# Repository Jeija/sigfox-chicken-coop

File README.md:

# Sigfox-Enabled Chicken Coop Controller

This repository contains hardware design files as well as firmware source code for a chicken coop controller board. The tiny controller (approx. 50x50mm) automatically opens and closes the chicken coop's door at scheduled times of day. It also transmits environmental data (e.g. temperature, humidity) via the Sigfox network and uses a solar chell to recharge a connected lead-acid battery.

The device operates in conjunction with a web service that uses the Sigfox API to retrieve the latest messages and that provides the current configuration and time of day to the controller. The web service has an end user-facing frontend that displays environmental data, device status information and lets the user configure door opening / closing times.

As a whole, this project probably isn't particularly useful for you since it represents a rather customized solution. Parts of it though may be of interest, e.g. the S2-LP transmitter design, the solar charger design or the firmware, which can be used as reference for how to integrate [renard-phy-s2lp](https://github.com/jeija/renard-phy-s2lp), an open source Sigfox PHY based on the open-source Sigfox stack [librenard](https://github.com/jeija/librenard) into an ESP32 project.

## Hardware Design
The controller mainly consists of the following components:

* An ESP32 microcontroller with integrated WiFi. WiFi functionality is only used for Over-the-Air (OTA) updating
* An S2-LP transceiver for Sigfox uplink and downlink, the RX balun / impedance matching is implemented with discrete components
* A LT3652 solar charging controller for lead-acid battery charging
* A RV-3029-C2 Real Time Clock (RTC)
* A BME280 environmental sensor for measuring temperature, pressure and humidity
* A DRV8872 as DC motor driver with an INA219 for motor current measurement (stall detection) for the door, as well as an input for a reed contact

Everything is mounted on a tiny 50x50mm PCB which fits nicely into an off-the-shelf plastic case (Strapubox A515).

The system is is powered by a 12V/7.2Ah lead-acid battery, which is recharged by the solar panel on top of the chicken coop. The Sigfox antenna is also mounted outside for an increased link budget.

* [**Download PDF Schematic**](hardware_pdf/schematic.pdf)
* [**Download PDF PCB Layout**](hardware_pdf/pcb.pdf)
* [**KiCad Sources**](hardware)

## Firmware
The controller firmware is based on [esp-idf](https://github.com/espressif/esp-idf).
Sigfox functionality is based on [renard-phy-s2lp](https://github.com/jeija/renard-phy-s2lp) and [renard-phy-s2lp-hal-esp32](https://github.com/jeija/renard-phy-s2lp-hal-esp32), which are included as git subprojects. This means that you need to make sure to clone this repository with the `--recursive` flag.

The firmware supports Over-the-Air (OTA) updates via WiFi. This functionality is based on [esp32-softap-ota](https://github.com/Jeija/esp32-softap-ota).

### Configuration
For now, Sigfox device ID and secret key are configured directly in `firmware/main/src/sigfox.c`, see variables `sigfox_key` and `sigfox_devid`. The provided default values are those that I published during [my Sigfox reverse engineering presentation](https://jeija.net/sigfox/), so they are known to be compromised!

Watch that presentation to learn more about device ID and secret key (=NAK) and where to obtain yours.

### Initial Build and Flash
Make sure you have a recent [esp-idf](https://github.com/espressif/esp-idf) version with support for cmake-based projects installed and configured properly. Then compile and flash this project as usual using the following steps:

* `idf.py all` to compile everything
* `idf.py -p /dev/ttyUSBX flash` to flash everything

### Over-the-Air Firmware Update
Compile the firmware as described previously and obtain the firmware binary at `firmware/build/sigfox-chicken-door.bin`.

Press both buttons of the chicken coop (up and down) simultaneously until the controller starts beeping regularly. This indicates that it is ready to receive updates.

The controller broadcasts a WiFi network with SSID `ESP32 OTA Update` and acts as an HTTP server. Connect to it, open the webpage at [192.168.4.1](http://192.168.4.1) and use the form to upload the binary. The webpage will display the update progress.

You can also use the `compile_and_post.sh` script to automatically perform the OTA firmware update, which might be useful during development.

## Web Component
The web component is a node.js application that runs on any web server that connects to the Sigfox API to provide downlinks (e.g. open / close time configuration) to the controller, analyze uplinks and visualize information.

This component is currently not public, but feel free to contact me if you have any questions regarding it.

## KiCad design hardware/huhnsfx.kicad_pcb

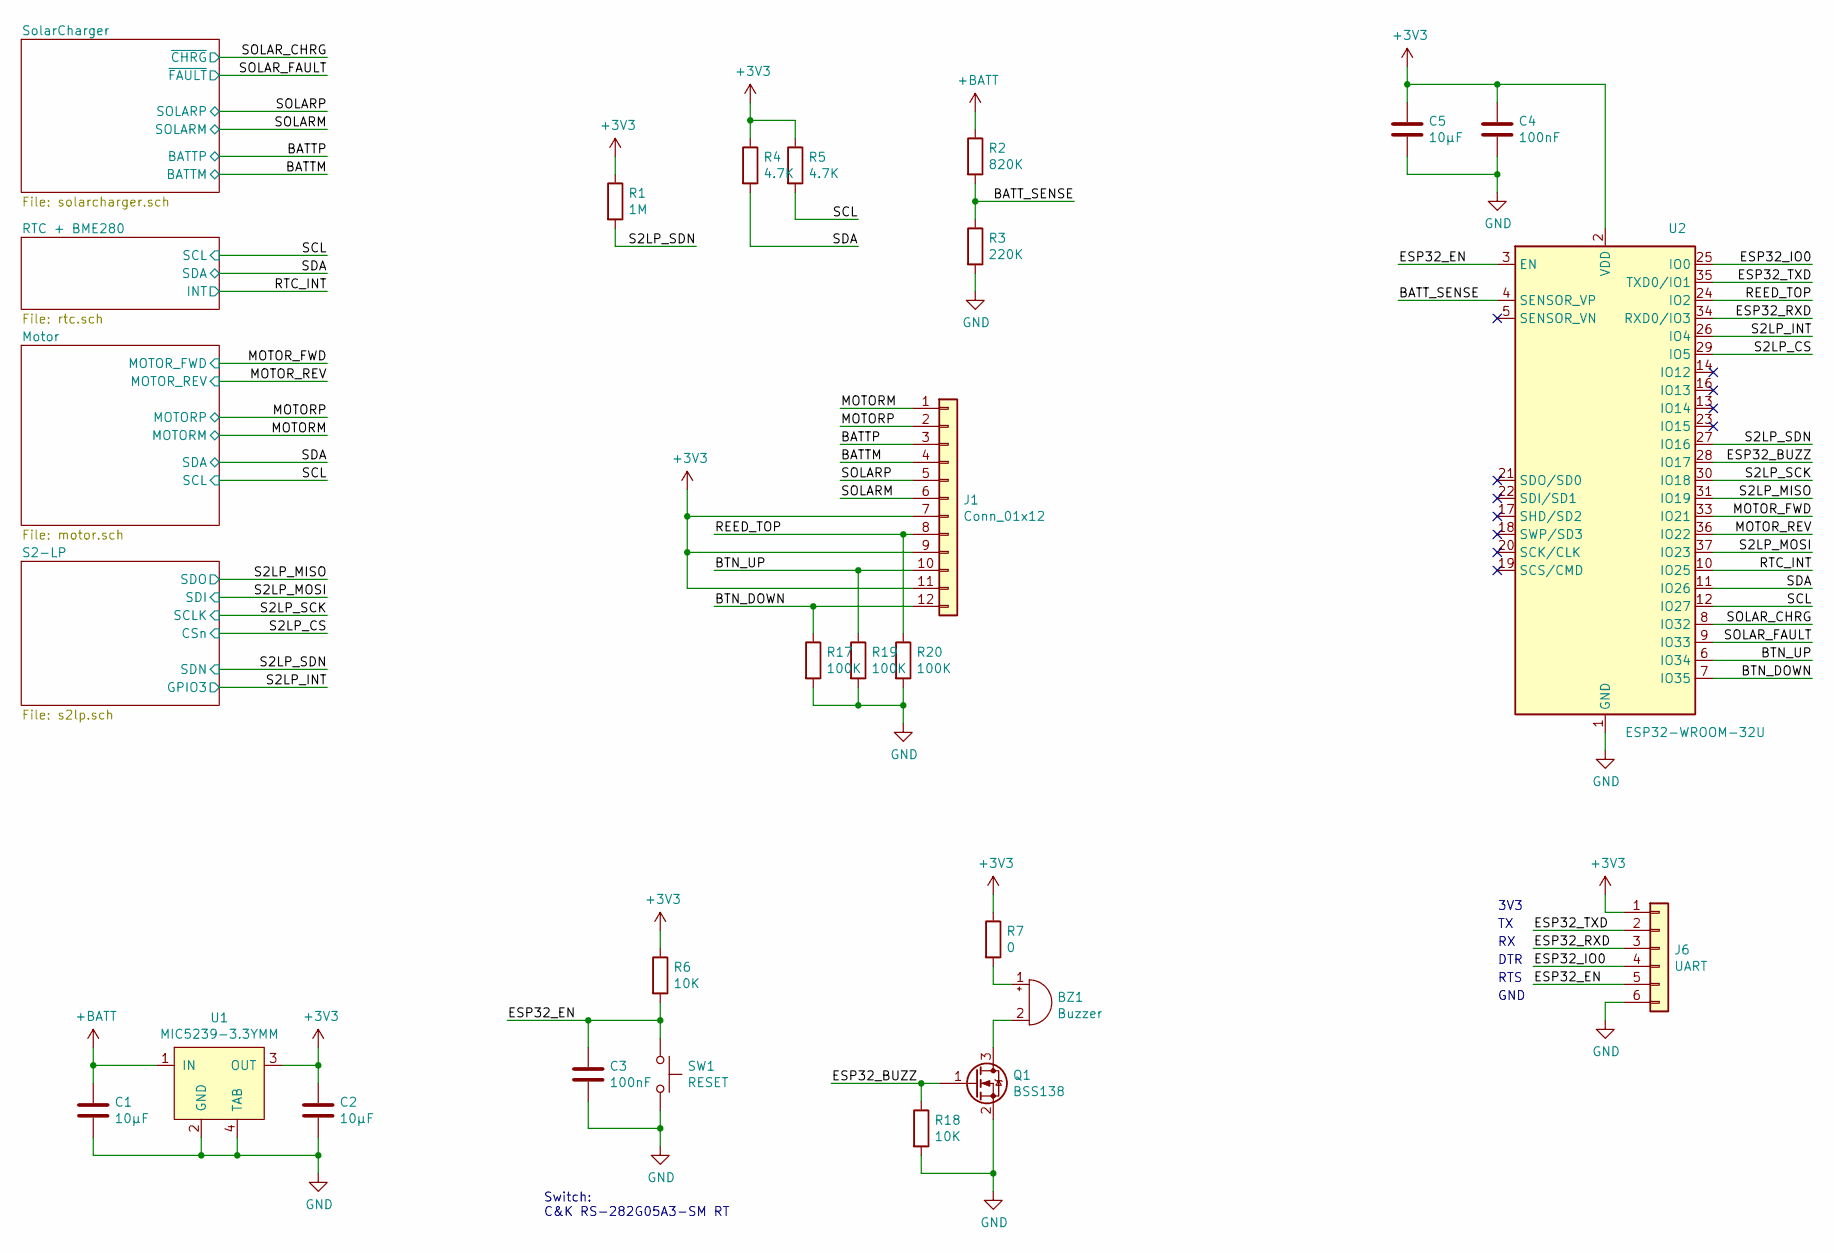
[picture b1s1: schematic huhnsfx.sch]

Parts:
BZ1: Buzzer; CMT-4023S
C1, C2, C5: 10µF; C_0603_1608Metric
C3, C4: 100nF; C_0603_1608Metric
J1: Conn_01x12; WAGO-233-512
J6: UART; PinHeader_2x03_P1.27mm_Vertical
Q1: BSS138; SOT-23
R1: 1M; R_0603_1608Metric
R2: 820K; R_0603_1608Metric
R3: 220K; R_0603_1608Metric
R4, R5: 4.7K; R_0603_1608Metric
R6, R18: 10K; R_0603_1608Metric
R7: 0; R_0603_1608Metric
R17, R19, R20: 100K; R_0603_1608Metric
SW1: RESET; SW_SPST_CK_RS282G05A3
U1: MIC5239-3.3YMM; SOT-223
U2: ESP32-WROOM-32U

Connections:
+3V3: C2.1, C4.1, C5.1, J1.7, J1.9, J1.11, J6.1, R1.1, R4.1, R5.1, R6.1, R7.1, U1.3 (OUT), U2.2 (VDD); also elsewhere on the board
+BATT: C1.1, J1.3, R2.1, U1.1 (IN); also elsewhere on the board
/BATT_SENSE: R2.2, R3.1, U2.4 (SENSOR_VP)
/BTN_DOWN: J1.12, R17.1, U2.7 (IO35)
/BTN_UP: J1.10, R19.1, U2.6 (IO34)
/ESP32_BUZZ: Q1.1 (G), R18.1, U2.28 (IO17)
/ESP32_EN: C3.1, J6.5, R6.2, SW1.1, U2.3 (EN)
/ESP32_IO0: J6.4, U2.25 (IO0)
/ESP32_RXD: J6.3, U2.34 (RXD0/IO3)
/ESP32_TXD: J6.2, U2.35 (TXD0/IO1)
/MOTORM: J1.1; also elsewhere on the board
/MOTORP: J1.2; also elsewhere on the board
/MOTOR_FWD: U2.33 (IO21); also elsewhere on the board
/MOTOR_REV: U2.36 (IO22); also elsewhere on the board
/REED_TOP: J1.8, R20.1, U2.24 (IO2)
/RTC_INT: U2.10 (IO25); also elsewhere on the board
/S2LP_CS: U2.29 (IO5); also elsewhere on the board
/S2LP_INT: U2.26 (IO4); also elsewhere on the board
/S2LP_MISO: U2.31 (IO19); also elsewhere on the board
/S2LP_MOSI: U2.37 (IO23); also elsewhere on the board
/S2LP_SCK: U2.30 (IO18); also elsewhere on the board
/S2LP_SDN: R1.2, U2.27 (IO16); also elsewhere on the board
/SCL: R5.2, U2.12 (IO27); also elsewhere on the board
/SDA: R4.2, U2.11 (IO26); also elsewhere on the board
/SOLARP: J1.5; also elsewhere on the board
/SOLAR_CHRG: U2.8 (IO32); also elsewhere on the board
/SOLAR_FAULT: U2.9 (IO33); also elsewhere on the board
GND: C1.2, C2.2, C3.2, C4.2, C5.2, J1.4, J1.6, J6.6, Q1.2 (S), R3.2, R17.2, R18.2, R19.2, R20.2, SW1.2, U1.2 (GND), U1.4 (TAB), U2.1 (GND), U2.15 (GND), U2.38 (GND), U2.39 (GND); also elsewhere on the board
unnamed: BZ1.1 (-), R7.2
unnamed: BZ1.2 (+), Q1.3 (D)

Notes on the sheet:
DTR
RTS
GND
3V3
Switch: C&K RS-282G05A3-SM RT

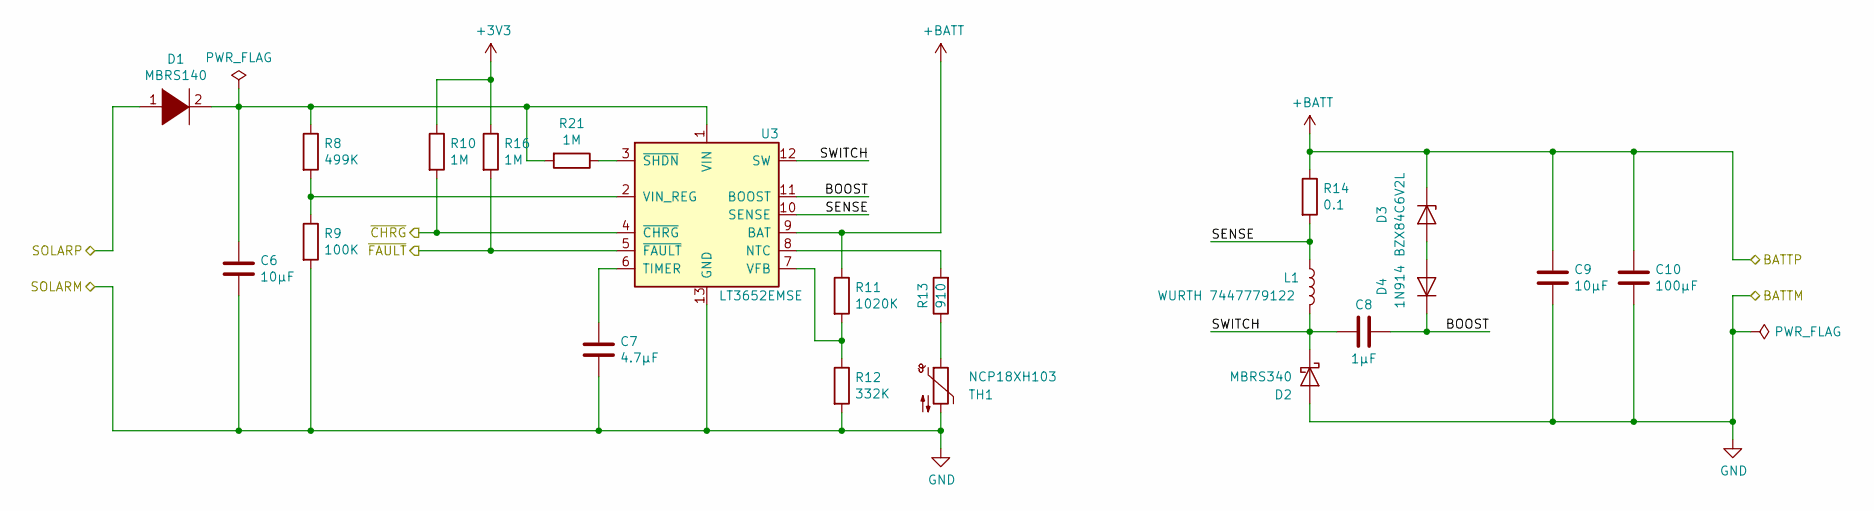
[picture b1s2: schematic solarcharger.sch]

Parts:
C6, C9: 10µF; C_0603_1608Metric
C7: 4.7µF; C_0603_1608Metric
C8: 1µF; C_0603_1608Metric
C10: 100µF; CP_Elec_6.3x3
D1: MBRS140; D_SMB
D2: MBRS340; D_SMC
D3: BZX84C6V2L; D_SOT-23_ANK
D4: 1N914; D_SOD-323F
L1: WURTH 7447779122; L_Wuerth_WE-PD-Typ-7345
R8: 499K; R_0603_1608Metric
R9: 100K; R_0603_1608Metric
R10, R16, R21: 1M; R_0603_1608Metric
R11: 1020K; R_0603_1608Metric
R12: 332K; R_0603_1608Metric
R13: 910; R_0603_1608Metric
R14: 0.1; R_0603_1608Metric
TH1: NCP18XH103; R_0603_1608Metric
U3: LT3652EMSE; MSOP-12-1EP_3x4mm_P0.65mm_EP1.65x2.85mm

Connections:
+3V3: R10.1, R16.1; also elsewhere on the board
+BATT: C9.1, C10.1, D3.1 (K), R11.1, R14.1, U3.9 (BAT); also elsewhere on the board
/SOLARP: D1.1 (K); also elsewhere on the board
/SOLAR_CHRG: R10.2, U3.4 (~CHRG); also elsewhere on the board
/SOLAR_FAULT: R16.2, U3.5 (~FAULT); also elsewhere on the board
/SolarCharger/BOOST: C8.1, D4.1 (K), U3.11 (BOOST)
/SolarCharger/SENSE: L1.1, R14.2, U3.10 (SENSE)
/SolarCharger/SWITCH: C8.2, D2.1 (K), L1.2, U3.12 (SW)
GND: C6.2, C7.2, C9.2, C10.2, D2.2 (A), R9.2, R12.2, TH1.2, U3.13 (GND); also elsewhere on the board
unnamed: C6.1, D1.2 (A), R8.1, R21.2, U3.1 (VIN)
unnamed: C7.1, U3.6 (TIMER)
unnamed: D3.2 (A), D4.2 (A)
unnamed: R8.2, R9.1, U3.2 (VIN_REG)
unnamed: R11.2, R12.1, U3.7 (VFB)
unnamed: R13.1, TH1.1
unnamed: R13.2, U3.8 (NTC)
unnamed: R21.1, U3.3 (~SHDN)

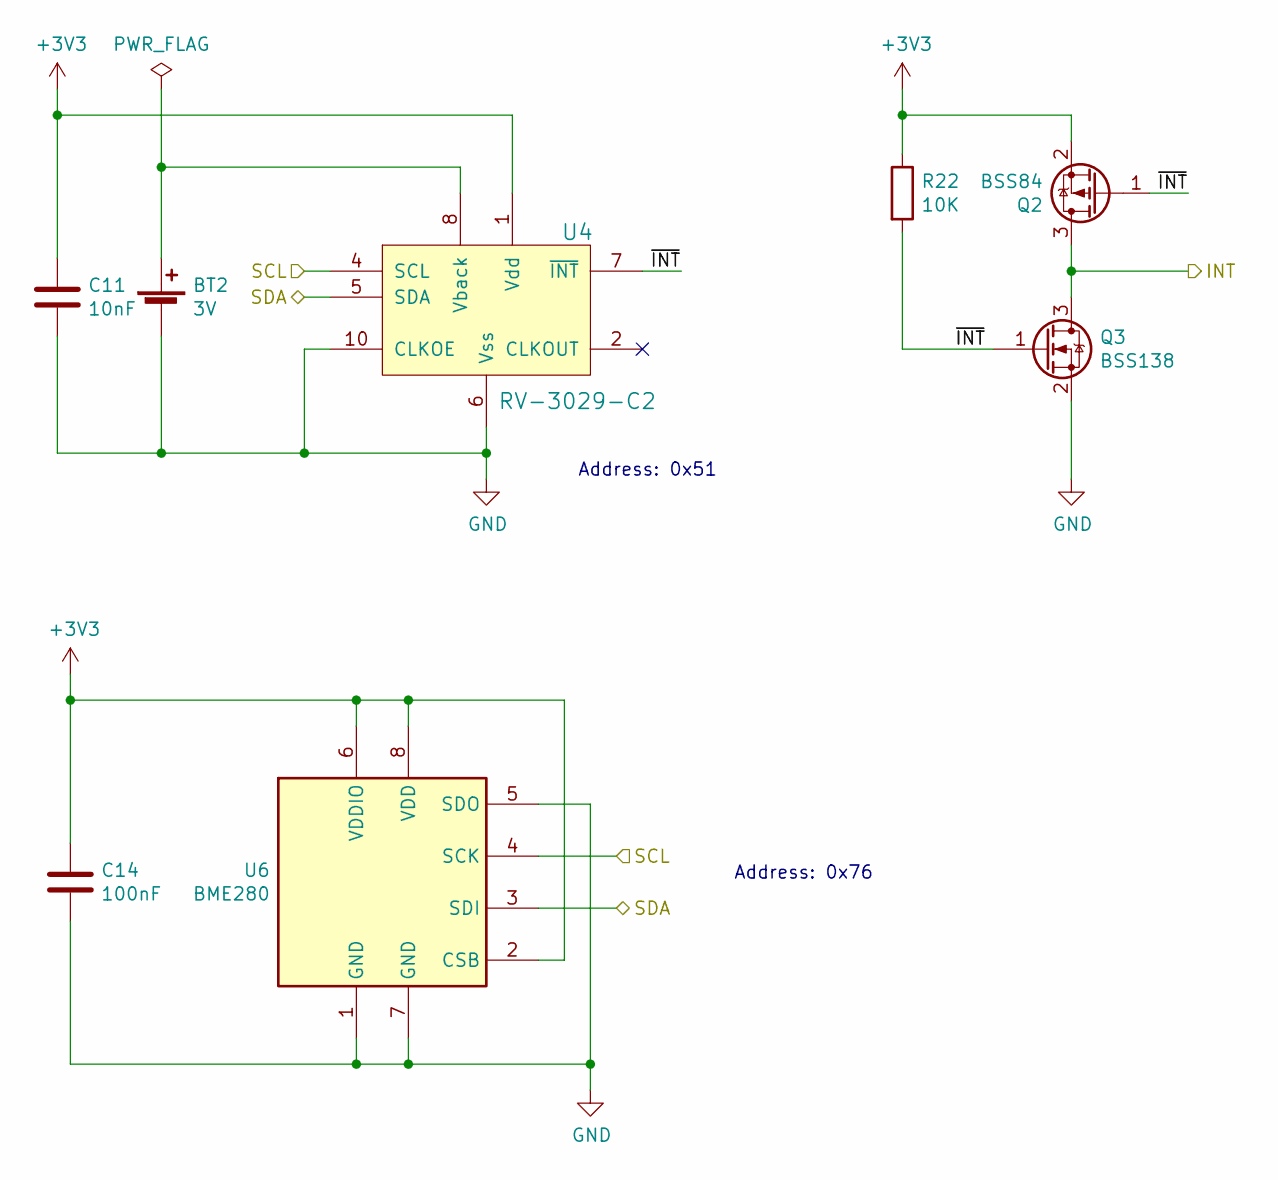
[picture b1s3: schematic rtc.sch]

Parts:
BT2: 3V; Molex_PicoBlade_53047-0210_1x02_P1.25mm_Vertical
C11: 10nF; C_0603_1608Metric
C14: 100nF; C_0603_1608Metric
Q2: BSS84; SOT-23
Q3: BSS138; SOT-23
R22: 10K; R_0603_1608Metric
U4: RV-3029-C2; rv3029
U6: BME280; Bosch_LGA-8_2.5x2.5mm_P0.65mm_ClockwisePinNumbering

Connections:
+3V3: C11.1, C14.1, Q2.2 (S), R22.1, U4.1 (Vdd), U6.2 (CSB), U6.6 (VDDIO), U6.8 (VDD); also elsewhere on the board
/RTC + BME280/~INT: Q2.1 (G), Q3.1 (G), R22.2, U4.7 (~INT)
/RTC_INT: Q2.3 (D), Q3.3 (D); also elsewhere on the board
/SCL: U4.4 (SCL), U6.4 (SCK); also elsewhere on the board
/SDA: U4.5 (SDA), U6.3 (SDI); also elsewhere on the board
GND: BT2.2 (-), C11.2, C14.2, Q3.2 (S), U4.6 (Vss), U4.10 (CLKOE), U6.1 (GND), U6.5 (SDO), U6.7 (GND); also elsewhere on the board
unnamed: BT2.1 (+), U4.8 (Vback)

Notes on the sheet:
Address: 0x76
Address: 0x51

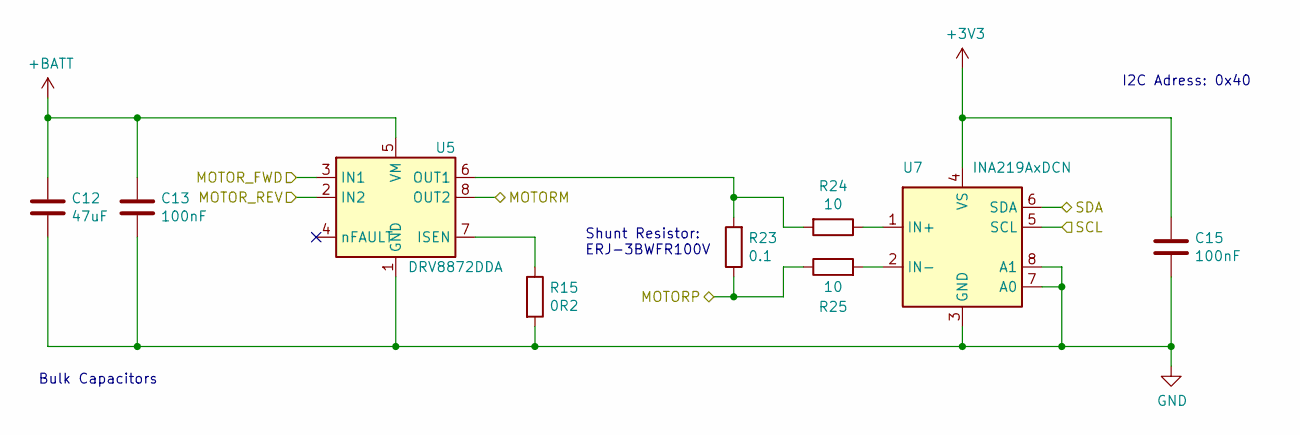
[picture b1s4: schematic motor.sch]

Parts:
C12: 47uF; C_1206_3216Metric
C13, C15: 100nF; C_0603_1608Metric
R15: 0R2; R_0603_1608Metric
R23: 0.1; R_0603_1608Metric
R24, R25: 10; R_0603_1608Metric
U5: DRV8872DDA; Texas_HTSOP-8-1EP_3.9x4.9mm_P1.27mm_EP2.95x4.9mm_Mask2.4x3.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
U7: INA219AxDCN; SOT-23-8

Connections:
+3V3: C15.1, U7.4 (VS); also elsewhere on the board
+BATT: C12.1, C13.1, U5.5 (VM); also elsewhere on the board
/MOTORM: U5.8 (OUT2); also elsewhere on the board
/MOTORP: R23.1, R25.1; also elsewhere on the board
/MOTOR_FWD: U5.3 (IN1); also elsewhere on the board
/MOTOR_REV: U5.2 (IN2); also elsewhere on the board
/SCL: U7.5 (SCL); also elsewhere on the board
/SDA: U7.6 (SDA); also elsewhere on the board
GND: C12.2, C13.2, C15.2, R15.2, U5.1 (GND), U5.9 (GND), U7.3 (GND), U7.7 (A0), U7.8 (A1); also elsewhere on the board
unnamed: R15.1, U5.7 (ISEN)
unnamed: R23.2, R24.2, U5.6 (OUT1)
unnamed: R24.1, U7.1 (IN+)
unnamed: R25.2, U7.2 (IN-)

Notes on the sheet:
Bulk Capacitors
I2C Adress: 0x40
Shunt Resistor: ERJ-3BWFR100V

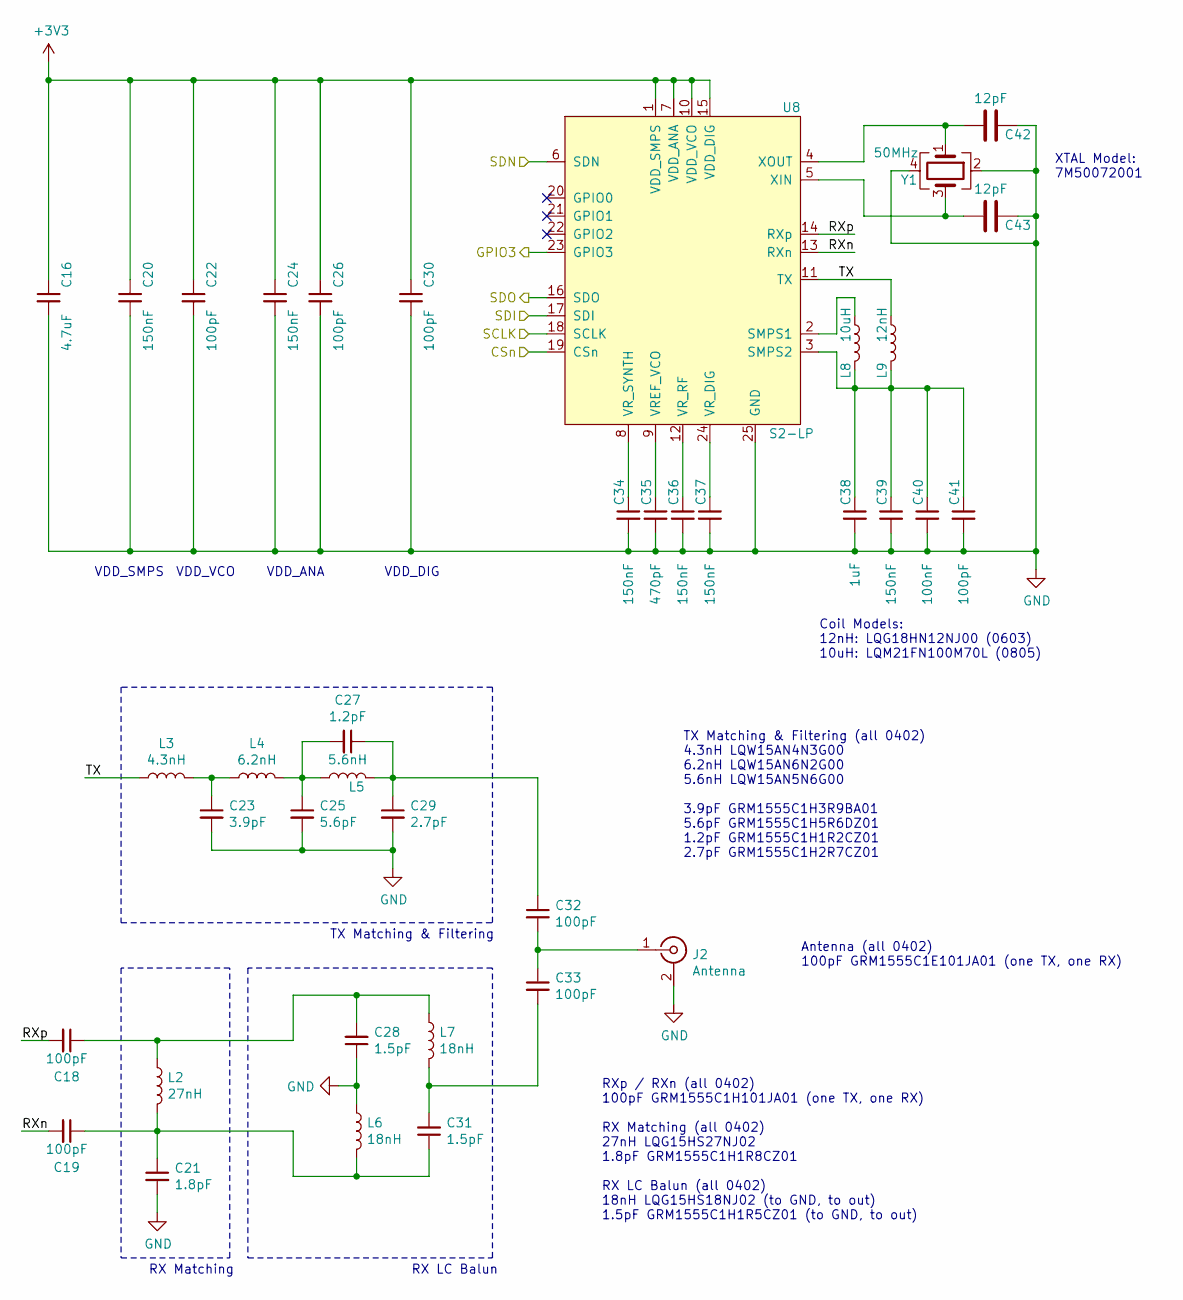
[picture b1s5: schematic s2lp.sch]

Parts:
C16: 4.7uF; C_0603_1608Metric
C18, C19, C32, C33: 100pF; C_0402_1005Metric
C20, C24, C34, C36, C37, C39: 150nF; C_0603_1608Metric
C21: 1.8pF; C_0402_1005Metric
C22, C26, C30, C41: 100pF; C_0603_1608Metric
C23: 3.9pF; C_0402_1005Metric
C25: 5.6pF; C_0402_1005Metric
C27: 1.2pF; C_0402_1005Metric
C28, C31: 1.5pF; C_0402_1005Metric
C29: 2.7pF; C_0402_1005Metric
C35: 470pF; C_0603_1608Metric
C38: 1uF; C_0603_1608Metric
C40: 100nF; C_0603_1608Metric
C42, C43: 12pF; C_0603_1608Metric
J2: Antenna; U.FL_Hirose_U.FL-R-SMT-1_Vertical
L2: 27nH; L_0402_1005Metric
L3: 4.3nH; L_0402_1005Metric
L4: 6.2nH; L_0402_1005Metric
L5: 5.6nH; L_0402_1005Metric
L6, L7: 18nH; L_0402_1005Metric
L8: 10uH; L_0805_2012Metric
L9: 12nH; L_0603_1608Metric
U8: S2-LP; QFN-24-1EP_4x4mm_P0.5mm_EP2.7x2.7mm_ThermalVias
Y1: 50MHz; Crystal_SMD_3225-4Pin_3.2x2.5mm

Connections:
+3V3: C16.1, C20.1, C22.1, C24.1, C26.1, C30.1, U8.1 (VDD_SMPS), U8.7 (VDD_ANA), U8.10 (VDD_VCO), U8.15 (VDD_DIG); also elsewhere on the board
/S2-LP/RXn: C19.2, U8.13 (RXn)
/S2-LP/RXp: C18.2, U8.14 (RXp)
/S2-LP/TX: L3.1, L9.1, U8.11 (TX)
/S2LP_CS: U8.19 (CSn); also elsewhere on the board
/S2LP_INT: U8.23 (GPIO3); also elsewhere on the board
/S2LP_MISO: U8.16 (SDO); also elsewhere on the board
/S2LP_MOSI: U8.17 (SDI); also elsewhere on the board
/S2LP_SCK: U8.18 (SCLK); also elsewhere on the board
/S2LP_SDN: U8.6 (SDN); also elsewhere on the board
GND: C16.2, C20.2, C21.2, C22.2, C23.2, C24.2, C25.2, C26.2, C28.1, C29.2, C30.2, C34.2, C35.2, C36.2, C37.2, C38.2, C39.2, C40.2, C41.2, C42.1, C43.1, J2.2 (Ext), L6.1, U8.25 (GND), Y1.2, Y1.4; also elsewhere on the board
unnamed: C18.1, C28.2, L2.1, L7.1
unnamed: C19.1, C21.1, C31.1, L2.2, L6.2
unnamed: C23.1, L3.2, L4.1
unnamed: C25.1, C27.2, L4.2, L5.1
unnamed: C27.1, C29.1, C32.1, L5.2
unnamed: C31.2, C33.2, L7.2
unnamed: C32.2, C33.1, J2.1 (In)
unnamed: C34.1, U8.8 (VR_SYNTH)
unnamed: C35.1, U8.9 (VREF_VCO)
unnamed: C36.1, U8.12 (VR_RF)
unnamed: C37.1, U8.24 (VR_DIG)
unnamed: C38.1, C39.1, C40.1, C41.1, L8.2, L9.2, U8.3 (SMPS2)
unnamed: C42.2, U8.4 (XOUT), Y1.1
unnamed: C43.2, U8.5 (XIN), Y1.3
unnamed: L8.1, U8.2 (SMPS1)

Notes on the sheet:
VDD_SMPS
VDD_VCO
VDD_ANA
VDD_DIG
Coil Models: 12nH: LQG18HN12NJ00 (0603) 10uH: LQM21FN100M70L (0805)
RX LC Balun
RX Matching
TX Matching & Filtering
XTAL Model: 7M50072001
TX Matching & Filtering (all 0402) 4.3nH LQW15AN4N3G00 6.2nH LQW15AN6N2G00 5.6nH LQW15AN5N6G00 3.9pF GRM1555C1H3R9BA01 5.6pF GRM1555C1H5R6DZ01 1.2pF GRM1555C1H1R2CZ01 2.7pF GRM1555C1H2R7CZ01
Antenna (all 0402) 100pF GRM1555C1E101JA01 (one TX, one RX)
RXp / RXn (all 0402) 100pF GRM1555C1H101JA01 (one TX, one RX) RX Matching (all 0402) 27nH LQG15HS27NJ02 1.8pF GRM1555C1H1R8CZ01 RX LC Balun (all 0402) 18nH LQG15HS18NJ02 (to GND, to out) 1.5pF GRM1555C1H1R5CZ01 (to GND, to out)

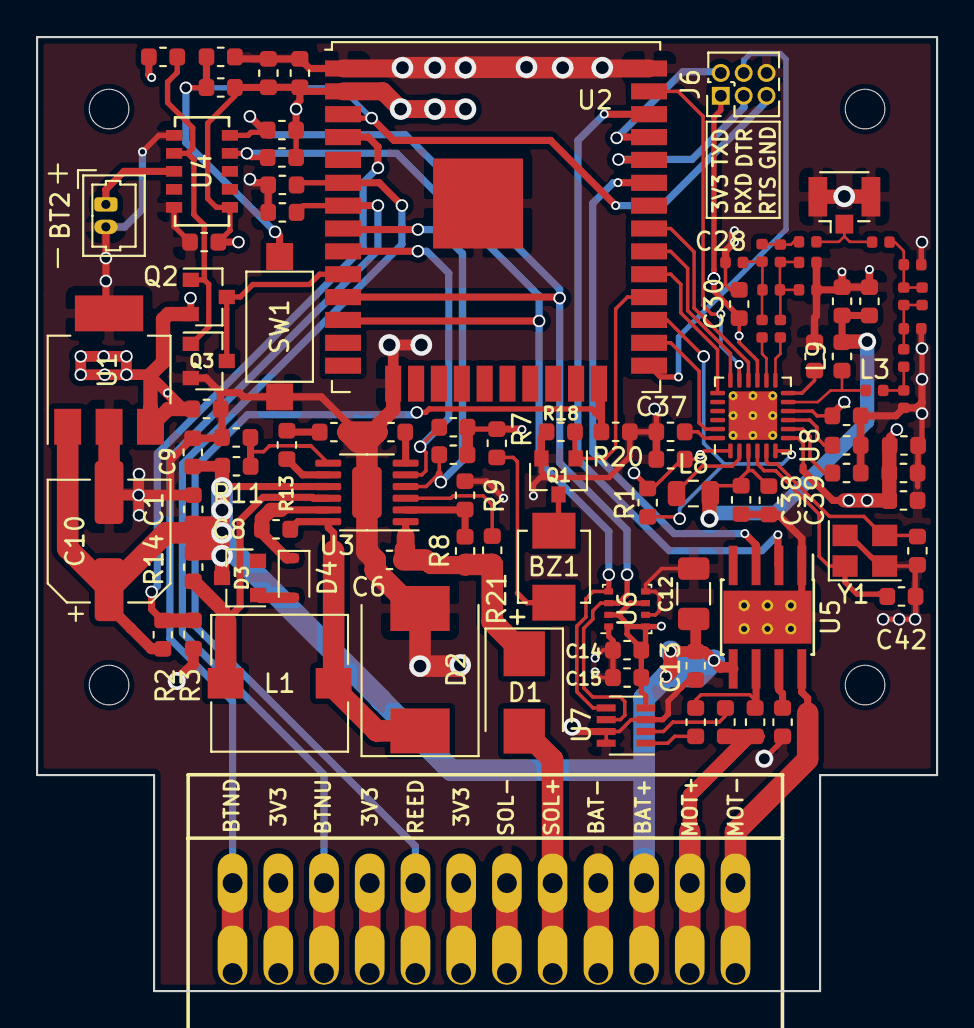
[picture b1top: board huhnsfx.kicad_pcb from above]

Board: 4 copper layers, 50.0 x 53.0 mm, 99 parts (0 on the bottom side), 65 nets.

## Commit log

2020-07-01 Initial upload with hardware design (no software yet)
2020-07-01 Add firmware, but without submodule (yet)
2020-07-01 Add submodules for firmware (renard-phy-s2lp, renard-phy-s2lp-hal-esp32)
2020-07-01 Minor README fixes
2020-07-02 Remove "true ||" in conditions (was used for debugging)
2020-07-02 Remove another line for debugging
    Enter deep sleep, do not restart
2020-07-28 Conversion to different door hardware (motor with end switches)
2020-07-29 Abort Sigfox TX / RX upon button interrupt / RTC interrupt
    Uses new platform-specific renard-phy-s2lp-hal-esp32 feature
2020-10-19 Remove stall detection once and for all, update renard libraries
2020-10-19 Switch back to 100bps uplink baudrate
2026-04-04 Update to latest esp-idf
2026-04-04 WIP: Adapt to new hardware
2026-04-04 More work on next generation
2026-04-05 Re-enable sigfox report after boot, downlink tested working
2026-04-05 Improve web interface
2026-04-05 Improve button handling
2026-04-05 Abort transmission if button is pressed
2026-04-05 Update hardware folder (opened with newer KiCad)
2026-04-05 Update renard-phy-s2lp-hal-esp32
